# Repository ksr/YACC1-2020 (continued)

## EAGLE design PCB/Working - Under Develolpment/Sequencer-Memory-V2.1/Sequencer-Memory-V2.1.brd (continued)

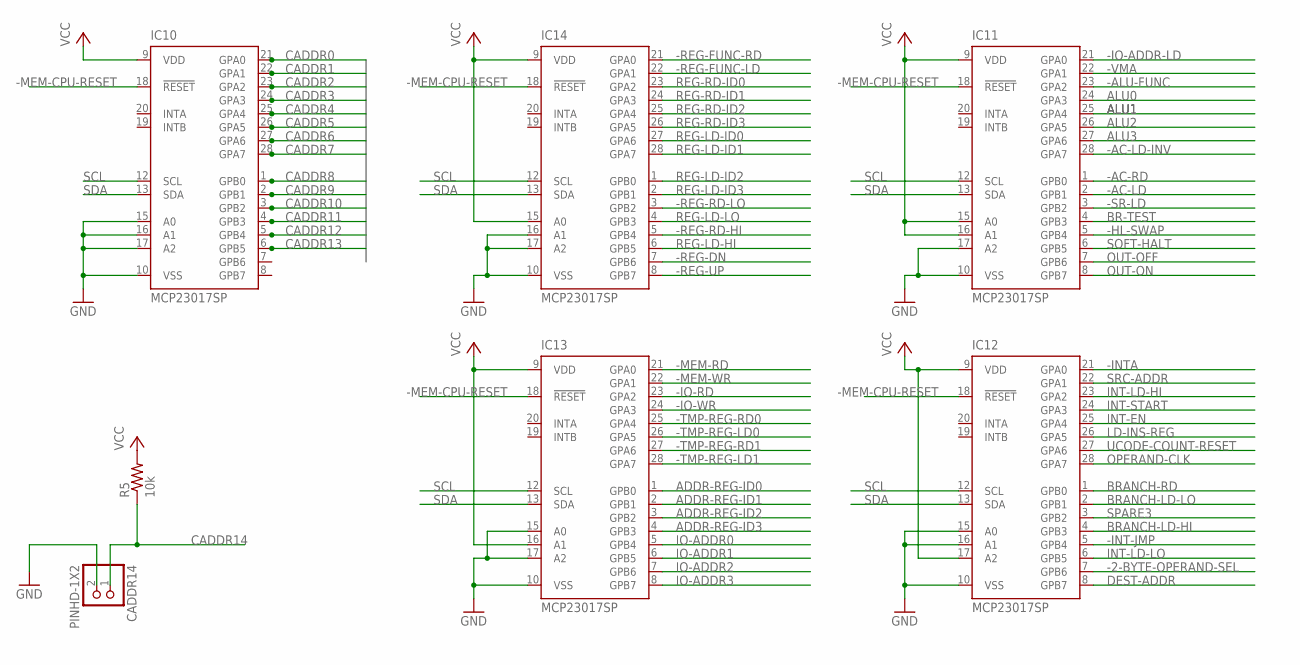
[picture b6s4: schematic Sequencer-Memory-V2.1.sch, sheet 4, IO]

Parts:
CADDR14: PINHD-1X2; 1X02
IC10, IC11, IC12, IC13, IC14: MCP23017SP; DIL28-3
R5: 10k; 0207/10

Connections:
-2-BYTE-OPERAND-SEL: IC12.7 (GPB6); also elsewhere on the board
-AC-LD: IC11.2 (GPB1); also elsewhere on the board
-AC-LD-INV: IC11.28 (GPA7); also elsewhere on the board
-AC-RD: IC11.1 (GPB0); also elsewhere on the board
-ALU-FUNC: IC11.23 (GPA2); also elsewhere on the board
-HL-SWAP: IC11.5 (GPB4); also elsewhere on the board
-INT-JMP: IC12.5 (GPB4); also elsewhere on the board
-INTA: IC12.21 (GPA0); also elsewhere on the board
-IO-ADDR-LD: IC11.21 (GPA0); also elsewhere on the board
-IO-RD: IC13.23 (GPA2); also elsewhere on the board
-IO-WR: IC13.24 (GPA3); also elsewhere on the board
-MEM-CPU-RESET: IC10.18 (!RESET), IC11.18 (!RESET), IC12.18 (!RESET), IC13.18 (!RESET), IC14.18 (!RESET); also elsewhere on the board
-MEM-RD: IC13.21 (GPA0); also elsewhere on the board
-MEM-WR: IC13.22 (GPA1); also elsewhere on the board
-REG-DN: IC14.7 (GPB6); also elsewhere on the board
-REG-FUNC-LD: IC14.22 (GPA1); also elsewhere on the board
-REG-FUNC-RD: IC14.21 (GPA0); also elsewhere on the board
-REG-RD-HI: IC14.5 (GPB4); also elsewhere on the board
-REG-RD-LO: IC14.3 (GPB2); also elsewhere on the board
-REG-UP: IC14.8 (GPB7); also elsewhere on the board
-SR-LD: IC11.3 (GPB2); also elsewhere on the board
-TMP-REG-LD0: IC13.26 (GPA5); also elsewhere on the board
-TMP-REG-LD1: IC13.28 (GPA7); also elsewhere on the board
-TMP-REG-RD0: IC13.25 (GPA4); also elsewhere on the board
-TMP-REG-RD1: IC13.27 (GPA6); also elsewhere on the board
-VMA: IC11.22 (GPA1); also elsewhere on the board
ADDR-REG-ID0: IC13.1 (GPB0); also elsewhere on the board
ADDR-REG-ID1: IC13.2 (GPB1); also elsewhere on the board
ADDR-REG-ID2: IC13.3 (GPB2); also elsewhere on the board
ADDR-REG-ID3: IC13.4 (GPB3); also elsewhere on the board
ALU0: IC11.24 (GPA3); also elsewhere on the board
ALU1: IC11.25 (GPA4); also elsewhere on the board
ALU2: IC11.26 (GPA5); also elsewhere on the board
ALU3: IC11.27 (GPA6); also elsewhere on the board
BR-TEST: IC11.4 (GPB3); also elsewhere on the board
BRANCH-LD-HI: IC12.4 (GPB3); also elsewhere on the board
BRANCH-LD-LO: IC12.2 (GPB1); also elsewhere on the board
BRANCH-RD: IC12.1 (GPB0); also elsewhere on the board
CADDR0: IC10.21 (GPA0); also elsewhere on the board
CADDR1: IC10.22 (GPA1); also elsewhere on the board
CADDR2: IC10.23 (GPA2); also elsewhere on the board
CADDR3: IC10.24 (GPA3); also elsewhere on the board
CADDR4: IC10.25 (GPA4); also elsewhere on the board
CADDR5: IC10.26 (GPA5); also elsewhere on the board
CADDR6: IC10.27 (GPA6); also elsewhere on the board
CADDR7: IC10.28 (GPA7); also elsewhere on the board
CADDR8: IC10.1 (GPB0); also elsewhere on the board
CADDR9: IC10.2 (GPB1); also elsewhere on the board
CADDR10: IC10.3 (GPB2); also elsewhere on the board
CADDR11: IC10.4 (GPB3); also elsewhere on the board
CADDR12: IC10.5 (GPB4); also elsewhere on the board
CADDR13: IC10.6 (GPB5); also elsewhere on the board
CADDR14: CADDR14.1, R5.1; also elsewhere on the board
DEST-ADDR: IC12.8 (GPB7); also elsewhere on the board
GND: CADDR14.2, IC10.10 (VSS), IC10.15 (A0), IC10.16 (A1), IC10.17 (A2), IC11.10 (VSS), IC11.17 (A2), IC12.10 (VSS), IC12.15 (A0), IC12.16 (A1), IC13.10 (VSS), IC13.15 (A0), IC13.17 (A2), IC14.10 (VSS), IC14.16 (A1), IC14.17 (A2); also elsewhere on the board
INT-EN: IC12.25 (GPA4); also elsewhere on the board
INT-LD-HI: IC12.23 (GPA2); also elsewhere on the board
INT-LD-LO: IC12.6 (GPB5); also elsewhere on the board
INT-START: IC12.24 (GPA3); also elsewhere on the board
IO-ADDR0: IC13.5 (GPB4); also elsewhere on the board
IO-ADDR1: IC13.6 (GPB5); also elsewhere on the board
IO-ADDR2: IC13.7 (GPB6); also elsewhere on the board
IO-ADDR3: IC13.8 (GPB7); also elsewhere on the board
LD-INS-REG: IC12.26 (GPA5); also elsewhere on the board
OPERAND-CLK: IC12.28 (GPA7); also elsewhere on the board
OUT-OFF: IC11.7 (GPB6); also elsewhere on the board
OUT-ON: IC11.8 (GPB7); also elsewhere on the board
REG-LD-HI: IC14.6 (GPB5); also elsewhere on the board
REG-LD-ID0: IC14.27 (GPA6); also elsewhere on the board
REG-LD-ID1: IC14.28 (GPA7); also elsewhere on the board
REG-LD-ID2: IC14.1 (GPB0); also elsewhere on the board
REG-LD-ID3: IC14.2 (GPB1); also elsewhere on the board
REG-LD-LO: IC14.4 (GPB3); also elsewhere on the board
REG-RD-ID0: IC14.23 (GPA2); also elsewhere on the board
REG-RD-ID1: IC14.24 (GPA3); also elsewhere on the board
REG-RD-ID2: IC14.25 (GPA4); also elsewhere on the board
REG-RD-ID3: IC14.26 (GPA5); also elsewhere on the board
SCL: IC10.12 (SCL), IC11.12 (SCL), IC12.12 (SCL), IC13.12 (SCL), IC14.12 (SCL); also elsewhere on the board
SDA: IC10.13 (SDA), IC11.13 (SDA), IC12.13 (SDA), IC13.13 (SDA), IC14.13 (SDA); also elsewhere on the board
SOFT-HALT: IC11.6 (GPB5); also elsewhere on the board
SPARE3: IC12.3 (GPB2); also elsewhere on the board
SRC-ADDR: IC12.22 (GPA1); also elsewhere on the board
UCODE-COUNT-RESET: IC12.27 (GPA6); also elsewhere on the board
VCC: IC10.9 (VDD), IC11.9 (VDD), IC11.15 (A0), IC11.16 (A1), IC12.9 (VDD), IC12.17 (A2), IC13.9 (VDD), IC13.16 (A1), IC14.9 (VDD), IC14.15 (A0), R5.2; also elsewhere on the board

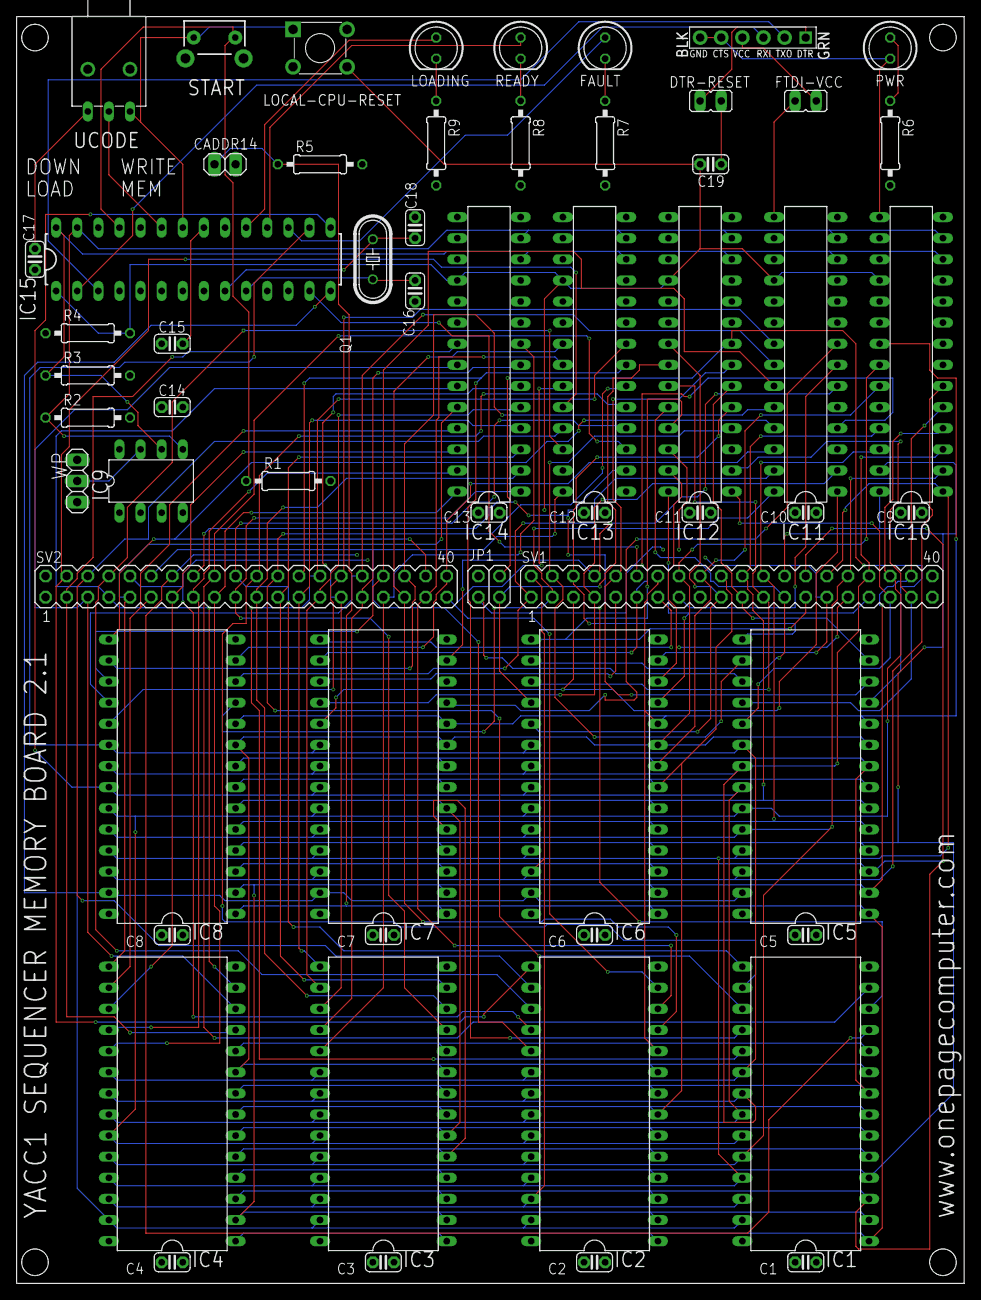
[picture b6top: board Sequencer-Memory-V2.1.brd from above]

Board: 4 copper layers, 114.0 x 152.4 mm, 59 parts (0 on the bottom side), 106 nets.

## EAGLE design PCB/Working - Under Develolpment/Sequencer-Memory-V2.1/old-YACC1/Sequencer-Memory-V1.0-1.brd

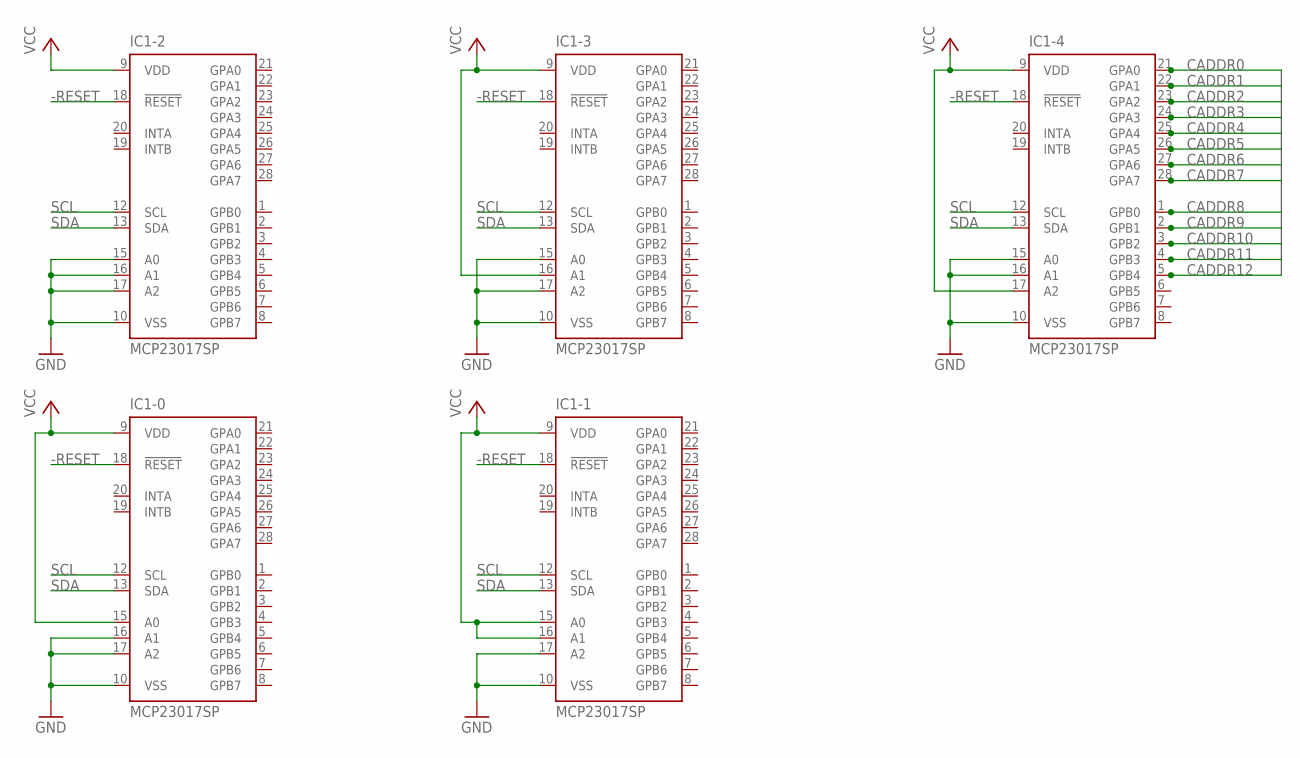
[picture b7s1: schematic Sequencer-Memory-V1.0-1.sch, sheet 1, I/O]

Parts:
IC1-0, IC1-1, IC1-2, IC1-3, IC1-4: MCP23017SP; DIL28-3

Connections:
-RESET: IC1-0.18 (!RESET), IC1-1.18 (!RESET), IC1-2.18 (!RESET), IC1-3.18 (!RESET), IC1-4.18 (!RESET); also elsewhere on the board
CADDR0: IC1-4.21 (GPA0); also elsewhere on the board
CADDR1: IC1-4.22 (GPA1); also elsewhere on the board
CADDR2: IC1-4.23 (GPA2); also elsewhere on the board
CADDR3: IC1-4.24 (GPA3); also elsewhere on the board
CADDR4: IC1-4.25 (GPA4); also elsewhere on the board
CADDR5: IC1-4.26 (GPA5); also elsewhere on the board
CADDR6: IC1-4.27 (GPA6); also elsewhere on the board
CADDR7: IC1-4.28 (GPA7); also elsewhere on the board
CADDR8: IC1-4.1 (GPB0); also elsewhere on the board
CADDR9: IC1-4.2 (GPB1); also elsewhere on the board
CADDR10: IC1-4.3 (GPB2); also elsewhere on the board
CADDR11: IC1-4.4 (GPB3); also elsewhere on the board
CADDR12: IC1-4.5 (GPB4); also elsewhere on the board
GND: IC1-0.10 (VSS), IC1-0.16 (A1), IC1-0.17 (A2), IC1-1.10 (VSS), IC1-1.17 (A2), IC1-2.10 (VSS), IC1-2.15 (A0), IC1-2.16 (A1), IC1-2.17 (A2), IC1-3.10 (VSS), IC1-3.15 (A0), IC1-3.17 (A2), IC1-4.10 (VSS), IC1-4.15 (A0), IC1-4.16 (A1); also elsewhere on the board
SCL: IC1-0.12 (SCL), IC1-1.12 (SCL), IC1-2.12 (SCL), IC1-3.12 (SCL), IC1-4.12 (SCL); also elsewhere on the board
SDA: IC1-0.13 (SDA), IC1-1.13 (SDA), IC1-2.13 (SDA), IC1-3.13 (SDA), IC1-4.13 (SDA); also elsewhere on the board
VCC: IC1-0.9 (VDD), IC1-0.15 (A0), IC1-1.9 (VDD), IC1-1.15 (A0), IC1-1.16 (A1), IC1-2.9 (VDD), IC1-3.9 (VDD), IC1-3.16 (A1), IC1-4.9 (VDD), IC1-4.17 (A2); also elsewhere on the board

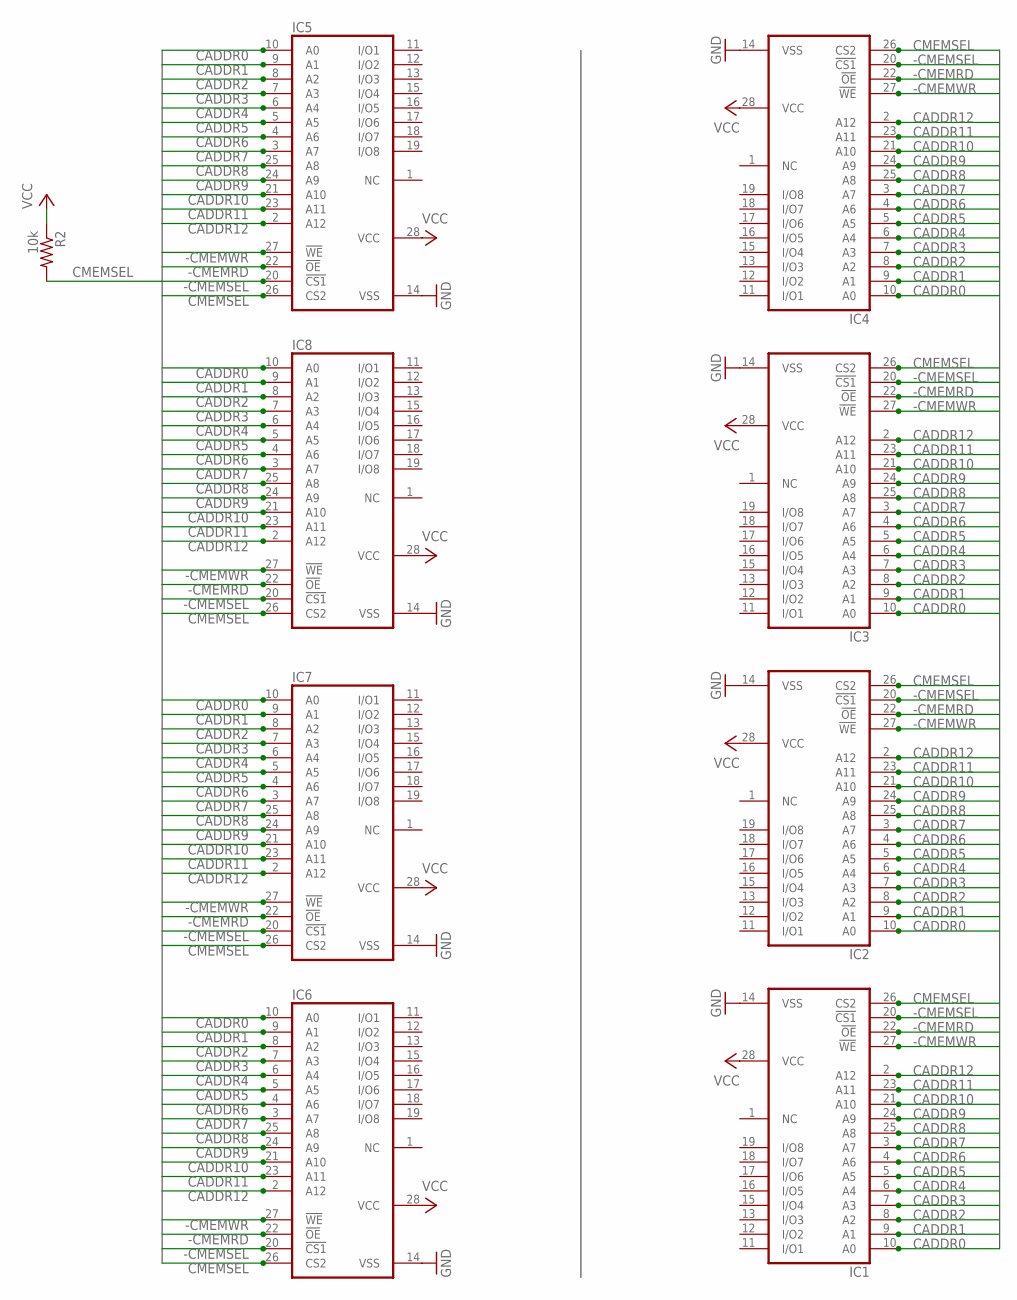
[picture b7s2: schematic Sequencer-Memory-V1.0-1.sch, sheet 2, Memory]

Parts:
IC1, IC2, IC3, IC4, IC5, IC6, IC7, IC8: 6264A; DIL28-6
R2: 10k; 0207/10

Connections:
-CMEMRD: IC1.22 (!OE), IC2.22 (!OE), IC3.22 (!OE), IC4.22 (!OE), IC5.22 (!OE), IC6.22 (!OE), IC7.22 (!OE), IC8.22 (!OE)
-CMEMSEL: IC1.20 (!CS1), IC2.20 (!CS1), IC3.20 (!CS1), IC4.20 (!CS1), IC5.20 (!CS1), IC6.20 (!CS1), IC7.20 (!CS1), IC8.20 (!CS1)
-CMEMWR: IC1.27 (!WE), IC2.27 (!WE), IC3.27 (!WE), IC4.27 (!WE), IC5.27 (!WE), IC6.27 (!WE), IC7.27 (!WE), IC8.27 (!WE)
CADDR0: IC1.10 (A0), IC2.10 (A0), IC3.10 (A0), IC4.10 (A0), IC5.10 (A0), IC6.10 (A0), IC7.10 (A0), IC8.10 (A0); also elsewhere on the board
CADDR1: IC1.9 (A1), IC2.9 (A1), IC3.9 (A1), IC4.9 (A1), IC5.9 (A1), IC6.9 (A1), IC7.9 (A1), IC8.9 (A1); also elsewhere on the board
CADDR2: IC1.8 (A2), IC2.8 (A2), IC3.8 (A2), IC4.8 (A2), IC5.8 (A2), IC6.8 (A2), IC7.8 (A2), IC8.8 (A2); also elsewhere on the board
CADDR3: IC1.7 (A3), IC2.7 (A3), IC3.7 (A3), IC4.7 (A3), IC5.7 (A3), IC6.7 (A3), IC7.7 (A3), IC8.7 (A3); also elsewhere on the board
CADDR4: IC1.6 (A4), IC2.6 (A4), IC3.6 (A4), IC4.6 (A4), IC5.6 (A4), IC6.6 (A4), IC7.6 (A4), IC8.6 (A4); also elsewhere on the board
CADDR5: IC1.5 (A5), IC2.5 (A5), IC3.5 (A5), IC4.5 (A5), IC5.5 (A5), IC6.5 (A5), IC7.5 (A5), IC8.5 (A5); also elsewhere on the board
CADDR6: IC1.4 (A6), IC2.4 (A6), IC3.4 (A6), IC4.4 (A6), IC5.4 (A6), IC6.4 (A6), IC7.4 (A6), IC8.4 (A6); also elsewhere on the board
CADDR7: IC1.3 (A7), IC2.3 (A7), IC3.3 (A7), IC4.3 (A7), IC5.3 (A7), IC6.3 (A7), IC7.3 (A7), IC8.3 (A7); also elsewhere on the board
CADDR8: IC1.25 (A8), IC2.25 (A8), IC3.25 (A8), IC4.25 (A8), IC5.25 (A8), IC6.25 (A8), IC7.25 (A8), IC8.25 (A8); also elsewhere on the board
CADDR9: IC1.24 (A9), IC2.24 (A9), IC3.24 (A9), IC4.24 (A9), IC5.24 (A9), IC6.24 (A9), IC7.24 (A9), IC8.24 (A9); also elsewhere on the board
CADDR10: IC1.21 (A10), IC2.21 (A10), IC3.21 (A10), IC4.21 (A10), IC5.21 (A10), IC6.21 (A10), IC7.21 (A10), IC8.21 (A10); also elsewhere on the board
CADDR11: IC1.23 (A11), IC2.23 (A11), IC3.23 (A11), IC4.23 (A11), IC5.23 (A11), IC6.23 (A11), IC7.23 (A11), IC8.23 (A11); also elsewhere on the board
CADDR12: IC1.2 (A12), IC2.2 (A12), IC3.2 (A12), IC4.2 (A12), IC5.2 (A12), IC6.2 (A12), IC7.2 (A12), IC8.2 (A12); also elsewhere on the board
CMEMSEL: IC1.26 (CS2), IC2.26 (CS2), IC3.26 (CS2), IC4.26 (CS2), IC5.26 (CS2), IC6.26 (CS2), IC7.26 (CS2), IC8.26 (CS2), R2.2
GND: IC1.14 (VSS), IC2.14 (VSS), IC3.14 (VSS), IC4.14 (VSS), IC5.14 (VSS), IC6.14 (VSS), IC7.14 (VSS), IC8.14 (VSS); also elsewhere on the board
VCC: IC1.28 (VCC), IC2.28 (VCC), IC3.28 (VCC), IC4.28 (VCC), IC5.28 (VCC), IC6.28 (VCC), IC7.28 (VCC), IC8.28 (VCC), R2.1; also elsewhere on the board

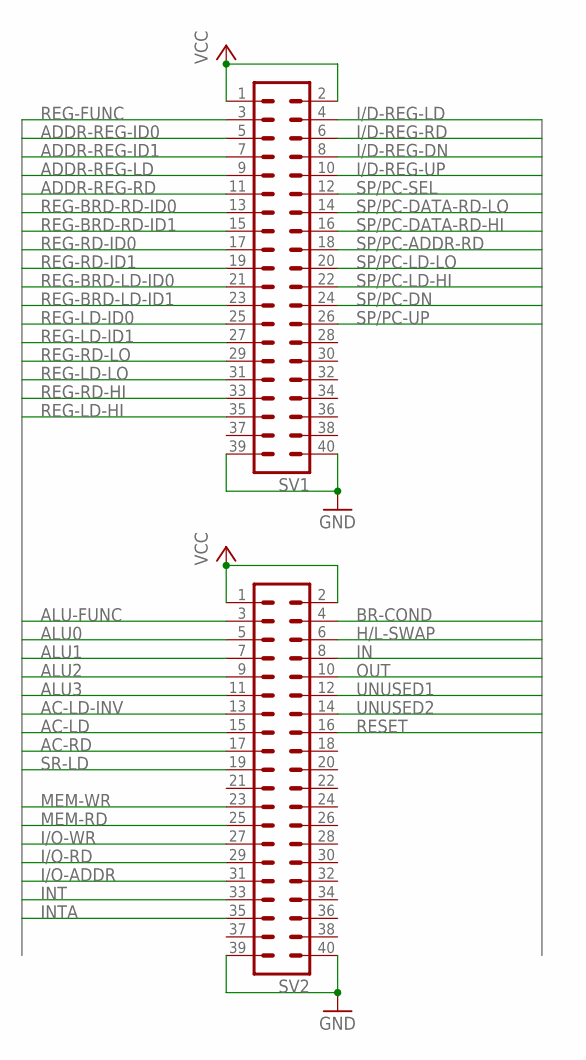
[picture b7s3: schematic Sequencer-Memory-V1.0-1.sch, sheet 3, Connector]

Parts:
SV1, SV2: MA20-2

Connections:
AC-LD: SV2.15; also elsewhere on the board
AC-LD-INV: SV2.13; also elsewhere on the board
AC-RD: SV2.17; also elsewhere on the board
ADDR-REG-ID0: SV1.5; also elsewhere on the board
ADDR-REG-ID1: SV1.7; also elsewhere on the board
ADDR-REG-LD: SV1.9; also elsewhere on the board
ADDR-REG-RD: SV1.11; also elsewhere on the board
ALU0: SV2.5; also elsewhere on the board
ALU1: SV2.7; also elsewhere on the board
ALU2: SV2.9; also elsewhere on the board
ALU3: SV2.11; also elsewhere on the board
ALU-FUNC: SV2.3; also elsewhere on the board
BR-COND: SV2.4; also elsewhere on the board
GND: SV1.39, SV1.40, SV2.39, SV2.40; also elsewhere on the board
H/L-SWAP: SV2.6; also elsewhere on the board
I/D-REG-DN: SV1.8; also elsewhere on the board
I/D-REG-LD: SV1.4; also elsewhere on the board
I/D-REG-RD: SV1.6; also elsewhere on the board
I/D-REG-UP: SV1.10; also elsewhere on the board
I/O-ADDR: SV2.31; also elsewhere on the board
I/O-RD: SV2.29; also elsewhere on the board
I/O-WR: SV2.27; also elsewhere on the board
IN: SV2.8; also elsewhere on the board
INT: SV2.33; also elsewhere on the board
INTA: SV2.35; also elsewhere on the board
MEM-RD: SV2.25; also elsewhere on the board
MEM-WR: SV2.23; also elsewhere on the board
OUT: SV2.10; also elsewhere on the board
REG-BRD-LD-ID0: SV1.21; also elsewhere on the board
REG-BRD-LD-ID1: SV1.23; also elsewhere on the board
REG-BRD-RD-ID0: SV1.13; also elsewhere on the board
REG-BRD-RD-ID1: SV1.15; also elsewhere on the board
REG-FUNC: SV1.3; also elsewhere on the board
REG-LD-HI: SV1.35; also elsewhere on the board
REG-LD-ID0: SV1.25; also elsewhere on the board
REG-LD-ID1: SV1.27; also elsewhere on the board
REG-LD-LO: SV1.31; also elsewhere on the board
REG-RD-HI: SV1.33; also elsewhere on the board
REG-RD-ID0: SV1.17; also elsewhere on the board
REG-RD-ID1: SV1.19; also elsewhere on the board
REG-RD-LO: SV1.29; also elsewhere on the board
RESET: SV2.16; also elsewhere on the board
SP/PC-ADDR-RD: SV1.18; also elsewhere on the board
SP/PC-DATA-RD-HI: SV1.16; also elsewhere on the board
SP/PC-DATA-RD-LO: SV1.14; also elsewhere on the board
SP/PC-DN: SV1.24; also elsewhere on the board
SP/PC-LD-HI: SV1.22; also elsewhere on the board
SP/PC-LD-LO: SV1.20; also elsewhere on the board
SP/PC-SEL: SV1.12; also elsewhere on the board
SP/PC-UP: SV1.26; also elsewhere on the board
SR-LD: SV2.19; also elsewhere on the board
UNUSED1: SV2.12; also elsewhere on the board
UNUSED2: SV2.14; also elsewhere on the board
VCC: SV1.1, SV1.2, SV2.1, SV2.2; also elsewhere on the board

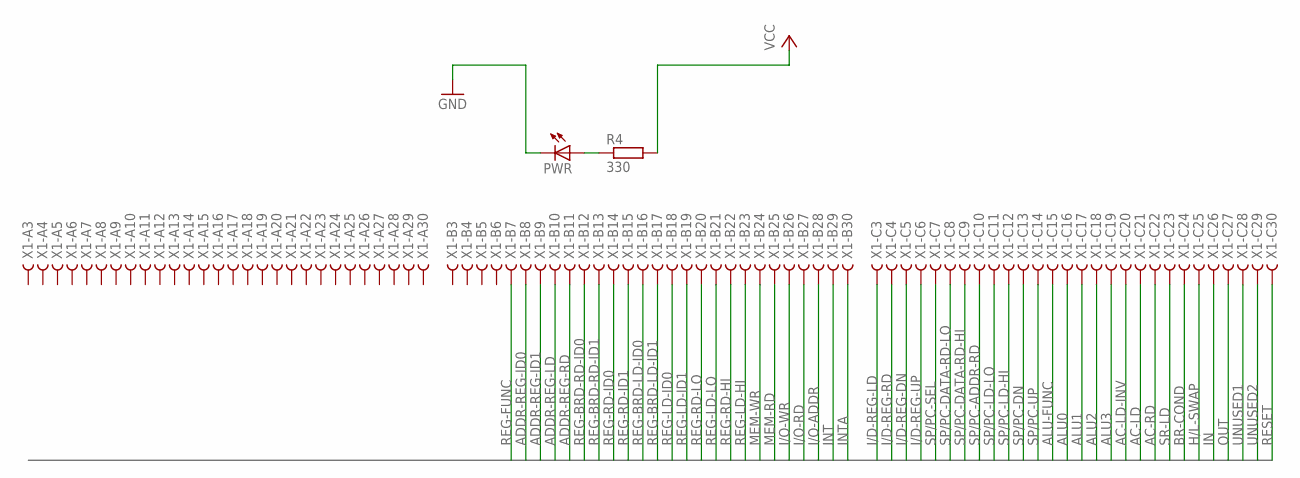
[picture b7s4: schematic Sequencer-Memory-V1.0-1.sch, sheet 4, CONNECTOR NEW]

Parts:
PWR: LED5MM
R4: 330; 0207/10
X1: FABC96R

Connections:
AC-LD: X1.C21; also elsewhere on the board
AC-LD-INV: X1.C20; also elsewhere on the board
AC-RD: X1.C22; also elsewhere on the board
ADDR-REG-ID0: X1.B8; also elsewhere on the board
ADDR-REG-ID1: X1.B9; also elsewhere on the board
ADDR-REG-LD: X1.B10; also elsewhere on the board
ADDR-REG-RD: X1.B11; also elsewhere on the board
ALU0: X1.C16; also elsewhere on the board
ALU1: X1.C17; also elsewhere on the board
ALU2: X1.C18; also elsewhere on the board
ALU3: X1.C19; also elsewhere on the board
ALU-FUNC: X1.C15; also elsewhere on the board
BR-COND: X1.C24; also elsewhere on the board
GND: PWR.K (C); also elsewhere on the board
H/L-SWAP: X1.C25; also elsewhere on the board
I/D-REG-DN: X1.C5; also elsewhere on the board
I/D-REG-LD: X1.C3; also elsewhere on the board
I/D-REG-RD: X1.C4; also elsewhere on the board
I/D-REG-UP: X1.C6; also elsewhere on the board
I/O-ADDR: X1.B28; also elsewhere on the board
I/O-RD: X1.B27; also elsewhere on the board
I/O-WR: X1.B26; also elsewhere on the board
IN: X1.C26; also elsewhere on the board
INT: X1.B29; also elsewhere on the board
INTA: X1.B30; also elsewhere on the board
MEM-RD: X1.B25; also elsewhere on the board
MEM-WR: X1.B24; also elsewhere on the board
unnamed: PWR.A, R4.1
OUT: X1.C27; also elsewhere on the board
REG-BRD-LD-ID0: X1.B16; also elsewhere on the board
REG-BRD-LD-ID1: X1.B17; also elsewhere on the board
REG-BRD-RD-ID0: X1.B12; also elsewhere on the board
REG-BRD-RD-ID1: X1.B13; also elsewhere on the board
REG-FUNC: X1.B7; also elsewhere on the board
REG-LD-HI: X1.B23; also elsewhere on the board
REG-LD-ID0: X1.B18; also elsewhere on the board
REG-LD-ID1: X1.B19; also elsewhere on the board
REG-LD-LO: X1.B21; also elsewhere on the board
REG-RD-HI: X1.B22; also elsewhere on the board
REG-RD-ID0: X1.B14; also elsewhere on the board
REG-RD-ID1: X1.B15; also elsewhere on the board
REG-RD-LO: X1.B20; also elsewhere on the board
RESET: X1.C30; also elsewhere on the board
SP/PC-ADDR-RD: X1.C10; also elsewhere on the board
SP/PC-DATA-RD-HI: X1.C9; also elsewhere on the board
SP/PC-DATA-RD-LO: X1.C8; also elsewhere on the board
SP/PC-DN: X1.C13; also elsewhere on the board
SP/PC-LD-HI: X1.C12; also elsewhere on the board
SP/PC-LD-LO: X1.C11; also elsewhere on the board
SP/PC-SEL: X1.C7; also elsewhere on the board
SP/PC-UP: X1.C14; also elsewhere on the board
SR-LD: X1.C23; also elsewhere on the board
UNUSED1: X1.C28; also elsewhere on the board
UNUSED2: X1.C29; also elsewhere on the board
VCC: R4.2; also elsewhere on the board

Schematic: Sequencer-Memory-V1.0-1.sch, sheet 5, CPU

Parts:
BUS-RESET: SWITCH-MOMENTARY-2SIDE_EZ; TACTILE-PTH-SIDEEZ
C11, C12: 20pf; C025-024X044
C13, C14, C15, C16, C17, C18, C19, C20, C21, C22, C23: 0.1; C025-024X044
CPU-RESET: TS-1109-7; SW4-6.2X6.2X5.0MM
DTR-RESET: JP1E; JP1
FTDI-VCC: JP1E; JP1
IC9: 24AA01P; DIL8
IC10: ATMEGA328P_PDIP; DIL28-3
JP3: FTDI_DEVICE; FTDI_DEVICE_SIDE
JP4: PINHD-1X3; 1X03
LED1, LED2, LED3, LED4, LED5: LED5MM
PWR1: LED5MM
Q1: 16Mhz; HC49/S
R1, R6, R11, R16, R17, R18: 330; 0207/10
R5, R12: 2.2k; 0207/10
R8, R25: 10k; 0207/10
S-A: 9070-1W
S-B: 9070-1W

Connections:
-RESET: C13.2, CPU-RESET.3 (B1), IC10.1 (PC6(/RESET)), R8.2; also elsewhere on the board
ARD-RXIN: IC10.2 (PD0(RXD)), JP3.P$3 (RXI)
ARD-TXOUT: IC10.3 (PD1(TXD)), JP3.P$2 (TXO)
GND: BUS-RESET.2, C11.1, C12.1, C14.1, C15.1, C16.1, C17.1, C18.1, C19.1, C20.1, C21.1, C22.1, C23.1, CPU-RESET.1 (A0), IC9.4 (GND), IC10.8 (GND), IC10.22 (GND), JP3.P$5 (CTS), JP3.P$6 (GND), JP4.1, PWR1.K (C), R6.2, R11.2, R16.2, R17.2, R18.2, S-A.3 (S), S-B.3 (S); also elsewhere on the board
unnamed: PWR1.A, R1.1
unnamed: C11.2, IC10.9 (PB6(XTAL1/TOSC1)), Q1.2
unnamed: C12.2, IC10.10 (PB7(XTAL2/TOSC2)), Q1.1
unnamed: C13.1, DTR-RESET.2
unnamed: C14.2, IC10.21 (AREF)
unnamed: IC10.19 (PB5(SCK)), LED1.A
unnamed: IC10.18 (PB4(MISO)), LED2.A
unnamed: IC10.17 (PB3(MOSI/OC2)), LED3.A
unnamed: IC10.16 (PB2(SS/OC1B)), LED4.A
unnamed: IC10.15 (PB1(OC1A)), LED5.A
unnamed: LED2.K (C), R11.1
unnamed: LED1.K (C), R16.1
unnamed: LED3.K (C), R6.1
unnamed: LED4.K (C), R17.1
unnamed: LED5.K (C), R18.1
unnamed: IC10.23 (PC0(ADC0)), S-A.2
unnamed: IC10.24 (PC1(ADC1)), S-B.2
unnamed: IC9.7 (WP), JP4.2
unnamed: DTR-RESET.1, JP3.P$1 (DTR)
unnamed: FTDI-VCC.2, JP3.P$4 (VCC)
unnamed: BUS-RESET.1, IC10.25 (PC2(ADC2)), R25.1
SCL: IC9.6 (SCL), IC10.28 (PC5(ADC5/SCL)), R5.1; also elsewhere on the board
SDA: IC9.5 (SDA), IC10.27 (PC4(ADC4/SDA)), R12.1; also elsewhere on the board
VCC: C15.2, C16.2, C17.2, C18.2, C19.2, C20.2, C21.2, C22.2, C23.2, FTDI-VCC.1, IC9.1 (A0), IC9.2 (A1), IC9.3 (A2), IC9.8 (VCC), IC10.7 (VCC), IC10.20 (AVCC), JP4.3, R1.2, R5.2, R8.1, R12.2, R25.2, S-A.1 (O), S-B.1 (O); also elsewhere on the board

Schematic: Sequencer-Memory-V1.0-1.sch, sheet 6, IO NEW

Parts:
IC1-5, IC11, IC12, IC13, IC14: MCP23017SP; DIL28-3
R3, R7, R9, R10: 10k; 0207/10

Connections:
-RESET: IC1-5.18 (!RESET), IC11.18 (!RESET), IC12.18 (!RESET), IC13.18 (!RESET), IC14.18 (!RESET), R3.1, R7.1, R9.1, R10.1; also elsewhere on the board
AC-LD: IC12.3 (GPB2); also elsewhere on the board
AC-LD-INV: IC12.2 (GPB1); also elsewhere on the board
AC-RD: IC12.4 (GPB3); also elsewhere on the board
ADDR-REG-ID0: IC14.22 (GPA1); also elsewhere on the board
ADDR-REG-ID1: IC14.23 (GPA2); also elsewhere on the board
ADDR-REG-LD: IC14.24 (GPA3); also elsewhere on the board
ADDR-REG-RD: IC14.25 (GPA4); also elsewhere on the board
ALU0: IC12.26 (GPA5); also elsewhere on the board
ALU1: IC12.27 (GPA6); also elsewhere on the board
ALU2: IC12.28 (GPA7); also elsewhere on the board
ALU3: IC12.1 (GPB0); also elsewhere on the board
ALU-FUNC: IC12.25 (GPA4); also elsewhere on the board
BIT0: IC11.1 (GPB0)
BIT1: IC11.2 (GPB1)
BIT2: IC11.3 (GPB2)
BIT3: IC11.4 (GPB3)
BIT4: IC11.5 (GPB4)
BIT5: IC11.6 (GPB5)
BIT6: IC11.7 (GPB6)
BIT7: IC11.8 (GPB7)
BR-COND: IC12.6 (GPB5); also elsewhere on the board
CADDR0: IC1-5.21 (GPA0); also elsewhere on the board
CADDR1: IC1-5.22 (GPA1); also elsewhere on the board
CADDR2: IC1-5.23 (GPA2); also elsewhere on the board
CADDR3: IC1-5.24 (GPA3); also elsewhere on the board
CADDR4: IC1-5.25 (GPA4); also elsewhere on the board
CADDR5: IC1-5.26 (GPA5); also elsewhere on the board
CADDR6: IC1-5.27 (GPA6); also elsewhere on the board
CADDR7: IC1-5.28 (GPA7); also elsewhere on the board
CADDR8: IC1-5.1 (GPB0); also elsewhere on the board
CADDR9: IC1-5.2 (GPB1); also elsewhere on the board
CADDR10: IC1-5.3 (GPB2); also elsewhere on the board
CADDR11: IC1-5.4 (GPB3); also elsewhere on the board
CADDR12: IC1-5.5 (GPB4); also elsewhere on the board
GND: IC1-5.10 (VSS), IC1-5.15 (A0), IC1-5.16 (A1), IC11.10 (VSS), IC11.16 (A1), IC12.10 (VSS), IC12.15 (A0), IC12.16 (A1), IC13.10 (VSS), IC13.17 (A2), IC14.10 (VSS), IC14.15 (A0), IC14.17 (A2); also elsewhere on the board
H/L-SWAP: IC12.7 (GPB6); also elsewhere on the board
I/D-REG-DN: IC13.3 (GPB2); also elsewhere on the board
I/D-REG-LD: IC13.1 (GPB0); also elsewhere on the board
I/D-REG-RD: IC13.2 (GPB1); also elsewhere on the board
I/D-REG-UP: IC13.4 (GPB3); also elsewhere on the board
I/O-ADDR: IC13.26 (GPA5); also elsewhere on the board
I/O-RD: IC13.25 (GPA4); also elsewhere on the board
I/O-WR: IC13.24 (GPA3); also elsewhere on the board
IN: IC12.8 (GPB7); also elsewhere on the board
IN-SWITCH: IC11.26 (GPA5)
INT: IC13.27 (GPA6); also elsewhere on the board
INTA: IC13.28 (GPA7); also elsewhere on the board
LEDS-LD: IC11.27 (GPA6)
MEM-RD: IC13.23 (GPA2); also elsewhere on the board
MEM-WR: IC13.22 (GPA1); also elsewhere on the board
OUT: IC11.21 (GPA0); also elsewhere on the board
OUT-LED: IC11.25 (GPA4)
REG-BRD-LD-ID0: IC14.2 (GPB1); also elsewhere on the board
REG-BRD-LD-ID1: IC14.3 (GPB2); also elsewhere on the board
REG-BRD-RD-ID0: IC14.26 (GPA5); also elsewhere on the board
REG-BRD-RD-ID1: IC14.27 (GPA6); also elsewhere on the board
REG-FUNC: IC14.21 (GPA0); also elsewhere on the board
REG-LD-HI: IC13.21 (GPA0); also elsewhere on the board
REG-LD-ID0: IC14.4 (GPB3); also elsewhere on the board
REG-LD-ID1: IC14.5 (GPB4); also elsewhere on the board
REG-LD-LO: IC14.7 (GPB6); also elsewhere on the board
REG-RD-HI: IC14.8 (GPB7); also elsewhere on the board
REG-RD-ID0: IC14.28 (GPA7); also elsewhere on the board
REG-RD-ID1: IC14.1 (GPB0); also elsewhere on the board
REG-RD-LO: IC14.6 (GPB5); also elsewhere on the board
RESET: IC11.24 (GPA3); also elsewhere on the board
SCL: IC1-5.12 (SCL), IC11.12 (SCL), IC12.12 (SCL), IC13.12 (SCL), IC14.12 (SCL); also elsewhere on the board
SDA: IC1-5.13 (SDA), IC11.13 (SDA), IC12.13 (SDA), IC13.13 (SDA), IC14.13 (SDA); also elsewhere on the board
SP/PC-ADDR-RD: IC13.8 (GPB7); also elsewhere on the board
SP/PC-DATA-RD-HI: IC13.7 (GPB6); also elsewhere on the board
SP/PC-DATA-RD-LO: IC13.6 (GPB5); also elsewhere on the board
SP/PC-DN: IC12.23 (GPA2); also elsewhere on the board
SP/PC-LD-HI: IC12.22 (GPA1); also elsewhere on the board
SP/PC-LD-LO: IC12.21 (GPA0); also elsewhere on the board
SP/PC-SEL: IC13.5 (GPB4); also elsewhere on the board
SP/PC-UP: IC12.24 (GPA3); also elsewhere on the board
SR-LD: IC12.5 (GPB4); also elsewhere on the board
SWITCHES-RD: IC11.28 (GPA7)
UNUSED1: IC11.22 (GPA1); also elsewhere on the board
UNUSED2: IC11.23 (GPA2); also elsewhere on the board
VCC: IC1-5.9 (VDD), IC1-5.17 (A2), IC11.9 (VDD), IC11.15 (A0), IC11.17 (A2), IC12.9 (VDD), IC12.17 (A2), IC13.9 (VDD), IC13.15 (A0), IC13.16 (A1), IC14.9 (VDD), IC14.16 (A1), R3.2, R7.2, R9.2, R10.2; also elsewhere on the board

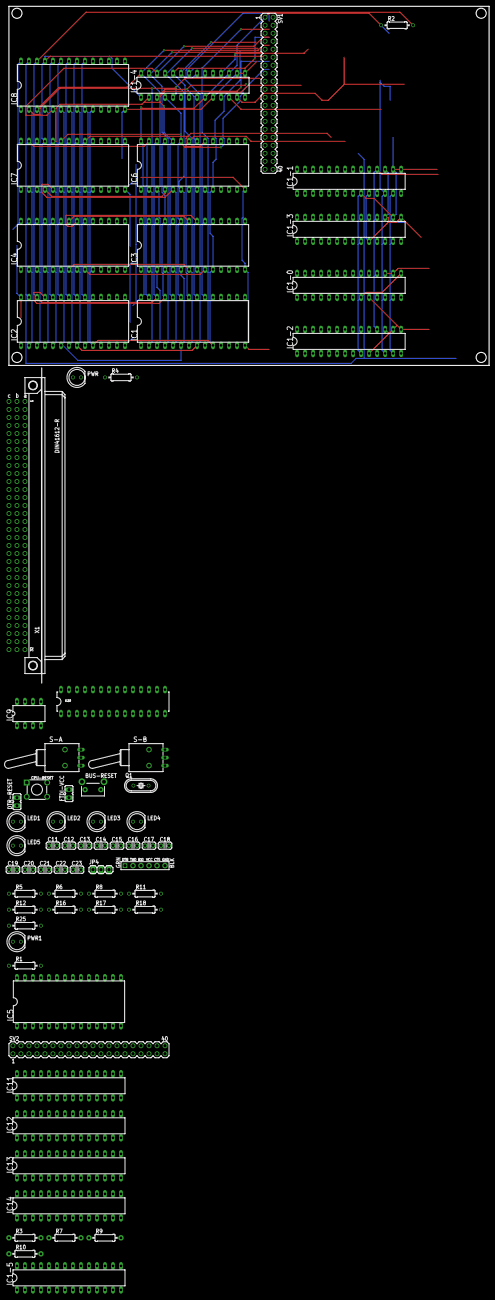
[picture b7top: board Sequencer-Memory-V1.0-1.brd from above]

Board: 2 copper layers, 152.4 x 214.8 mm, 68 parts (0 on the bottom side), 98 nets.

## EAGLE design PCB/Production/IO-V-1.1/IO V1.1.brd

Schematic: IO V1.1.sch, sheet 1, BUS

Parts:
C5, C6, C7, C8, C9, C10, C11, C12, C13, C14, C15, C16, C17: C-US025-024X044; C025-024X044
IC7: 74LS00N; DIL14
IC11: 74LS10N; DIL14
PWR: LED5MM
R2: 330; 0207/10
X1: FABC96R

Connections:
-AC-LD: X1.C22
-AC-LD-INV: X1.C20
-AC-RD: X1.C21
-ALU-FUNC: X1.C15
-BUS-EN: X1.C28
-HL-SWAP: X1.C25
-INT: X1.C13; also elsewhere on the board
-INTA: X1.C14
-IO-ADDR-LD: X1.C11
-IO-RD: X1.B25; also elsewhere on the board
-IO-WR: X1.B26; also elsewhere on the board
-MEM-RD: X1.B23
-MEM-WR: X1.B24
-REG-DN: X1.B21
-REG-FUNC-LD: X1.B8
-REG-FUNC-RD: X1.B7
-REG-LD-HI: X1.B20
-REG-LD-LO: X1.B18
-REG-RD-HI: X1.B19
-REG-RD-LO: X1.B17
-REG-UP: X1.B22
-RESET: X1.C30; also elsewhere on the board
-RUN: X1.C29
-SR-LD: X1.C23
-TMP-REG-LD0: X1.B28
-TMP-REG-LD1: X1.B30
-TMP-REG-RD0: X1.B27
-TMP-REG-RD1: X1.B29
-VMA: X1.C12
ADDR0: X1.A3
ADDR1: X1.A4
ADDR2: X1.A5
ADDR3: X1.A6
ADDR4: X1.A7
ADDR5: X1.A8
ADDR6: X1.A9
ADDR7: X1.A10
ADDR8: X1.A11
ADDR9: X1.A12
ADDR10: X1.A13
ADDR11: X1.A14
ADDR12: X1.A15
ADDR13: X1.A16
ADDR14: X1.A17
ADDR15: X1.A18
ADDR-REG-ID0: X1.C3
ADDR-REG-ID1: X1.C4
ADDR-REG-ID2: X1.C5
ADDR-REG-ID3: X1.C6
ALU0: X1.C16
ALU1: X1.C17
ALU2: X1.C18
ALU3: X1.C19
BR-COND: X1.C24
DATA0: X1.A19; also elsewhere on the board
DATA1: X1.A20; also elsewhere on the board
DATA2: X1.A21; also elsewhere on the board
DATA3: X1.A22; also elsewhere on the board
DATA4: X1.A23; also elsewhere on the board
DATA5: X1.A24; also elsewhere on the board
DATA6: X1.A25; also elsewhere on the board
DATA7: X1.A26; also elsewhere on the board
DATA8: X1.A27
DATA9: X1.A28
DATA10: X1.A29
DATA11: X1.A30
DATA12: X1.B3
DATA13: X1.B4
DATA14: X1.B5
DATA15: X1.B6
GND: C5.2, C6.2, C7.2, C8.2, C9.2, C10.2, C11.2, C12.2, C13.2, C14.2, C15.2, C16.2, C17.2, IC7.7 (GND), IC7.9 (I0), IC7.10 (I1), IC11.3 (I0), IC11.4 (I1), IC11.5 (I2), IC11.7 (GND), IC11.9 (I0), IC11.10 (I1), IC11.11 (I2), PWR.K (C), X1.A1, X1.A32, X1.B1, X1.B32, X1.C1, X1.C32; also elsewhere on the board
IN: X1.C26; also elsewhere on the board
IO-ADDR0: X1.C7; also elsewhere on the board
IO-ADDR1: X1.C8; also elsewhere on the board
IO-ADDR2: X1.C9; also elsewhere on the board
IO-ADDR3: X1.C10; also elsewhere on the board
unnamed: PWR.A, R2.1
OUT: X1.C27; also elsewhere on the board
REG-LD-ID0: X1.B13
REG-LD-ID1: X1.B14
REG-LD-ID2: X1.B15
REG-LD-ID3: X1.B16
REG-RD-ID0: X1.B9
REG-RD-ID1: X1.B10
REG-RD-ID2: X1.B11
REG-RD-ID3: X1.B12
VCC: C5.1, C6.1, C7.1, C8.1, C9.1, C10.1, C11.1, C12.1, C13.1, C14.1, C15.1, C16.1, C17.1, IC7.14 (VCC), IC11.14 (VCC), R2.2, X1.A2, X1.A31, X1.B2, X1.B31, X1.C2, X1.C31; also elsewhere on the board

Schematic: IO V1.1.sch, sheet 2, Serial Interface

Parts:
C1, C2, C3, C4: CPOL-USE2,5-6E; E2,5-6E
IC1: XR-16C550P; DIL40
IC2: MAX232; DIL16
IC8: 74LS06N; DIL14
INT: PINHD-1X2; 1X02
J1: DB9FEMALE; DB9
JP1: PINHD-2X3; 2X03
RN2: RNX6; RN-7
Y1: ECS-2100AX-200

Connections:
-INT: IC8.12 (O), RN2.2; also elsewhere on the board
DATA0: IC1.1 (D0); also elsewhere on the board
DATA1: IC1.2 (D1); also elsewhere on the board
DATA2: IC1.3 (D2); also elsewhere on the board
DATA3: IC1.4 (D3); also elsewhere on the board
DATA4: IC1.5 (D4); also elsewhere on the board
DATA5: IC1.6 (D5); also elsewhere on the board
DATA6: IC1.7 (D6); also elsewhere on the board
DATA7: IC1.8 (D7); also elsewhere on the board
GND: C4.+, IC1.14 (CS2~), IC1.20 (GND), IC1.25 (AS~), IC2.15 (GND), IC8.7 (GND), J1.5, Y1.4 (GND); also elsewhere on the board
ICLK: IC1.9 (RCLK), IC1.15 (BAUDOUT~)
IO-RD: IC1.22 (IOR); also elsewhere on the board
IO-SELDATA: IC1.12 (CS0); also elsewhere on the board
IO-WR: IC1.19 (IOW); also elsewhere on the board
unnamed: IC1.16 (XTAL1), Y1.5 (OUTPUT)
unnamed: J1.2, JP1.4
unnamed: J1.3, JP1.3
unnamed: IC1.11 (TX), IC2.11 (T1IN)
unnamed: C2.-, IC2.5 (C2-)
unnamed: C2.+, IC2.4 (C2+)
unnamed: IC1.30 (INT), INT.1
unnamed: C1.-, IC2.3 (C1-)
unnamed: C1.+, IC2.1 (C1+)
unnamed: C3.+, IC2.2 (V+)
unnamed: C4.-, IC2.6 (V-)
unnamed: IC8.13 (I), INT.2
RESET: IC1.35 (RESET); also elsewhere on the board
RX: IC1.10 (RX), IC2.12 (R1OUT)
RX-IN: IC2.13 (R1IN), JP1.1, JP1.6
TX-OUT: IC2.14 (T1OUT), JP1.2, JP1.5
UART-A0: IC1.28 (A0); also elsewhere on the board
UART-A1: IC1.27 (A1); also elsewhere on the board
UART-A2: IC1.26 (A2); also elsewhere on the board
UART-CS: IC1.13 (CS1); also elsewhere on the board
VCC: C3.-, IC1.18 (IOW~), IC1.21 (IOR~), IC1.36 (CTS~), IC1.37 (DSR~), IC1.38 (CD~), IC1.39 (RI~), IC1.40 (VCC), IC2.16 (VCC), IC8.14 (VCC), Y1.8 (+5VDC); also elsewhere on the board
